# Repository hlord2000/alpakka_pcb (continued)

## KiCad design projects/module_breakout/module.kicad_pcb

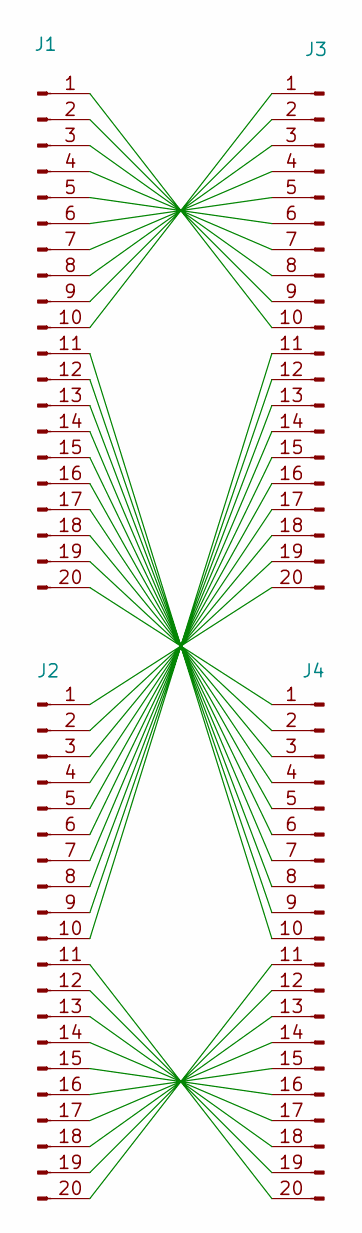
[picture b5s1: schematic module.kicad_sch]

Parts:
J1, J2: Conn_01x20_Pin; Hirose_DF12NB_receptacle; LCSC C2917814
J3, J4: Conn_01x20_Pin; PinHeader_1x20_P2.54mm_Vertical

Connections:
unnamed: J1.1, J3.10
unnamed: J1.2, J3.9
unnamed: J1.3, J3.8
unnamed: J1.4, J3.7
unnamed: J1.5, J3.6
unnamed: J1.6, J3.5
unnamed: J1.7, J3.4
unnamed: J1.8, J3.3
unnamed: J1.9, J3.2
unnamed: J1.10, J3.1
unnamed: J1.11, J4.10
unnamed: J1.12, J4.9
unnamed: J1.13, J4.8
unnamed: J1.14, J4.7
unnamed: J1.15, J4.6
unnamed: J1.16, J4.5
unnamed: J1.17, J4.4
unnamed: J1.18, J4.3
unnamed: J1.19, J4.2
unnamed: J1.20, J4.1
unnamed: J2.1, J3.20
unnamed: J2.2, J3.19
unnamed: J2.3, J3.18
unnamed: J2.4, J3.17
unnamed: J2.5, J3.16
unnamed: J2.6, J3.15
unnamed: J2.7, J3.14
unnamed: J2.8, J3.13
unnamed: J2.9, J3.12
unnamed: J2.10, J3.11
unnamed: J2.11, J4.20
unnamed: J2.12, J4.19
unnamed: J2.13, J4.18
unnamed: J2.14, J4.17
unnamed: J2.15, J4.16
unnamed: J2.16, J4.15
unnamed: J2.17, J4.14
unnamed: J2.18, J4.13
unnamed: J2.19, J4.12
unnamed: J2.20, J4.11

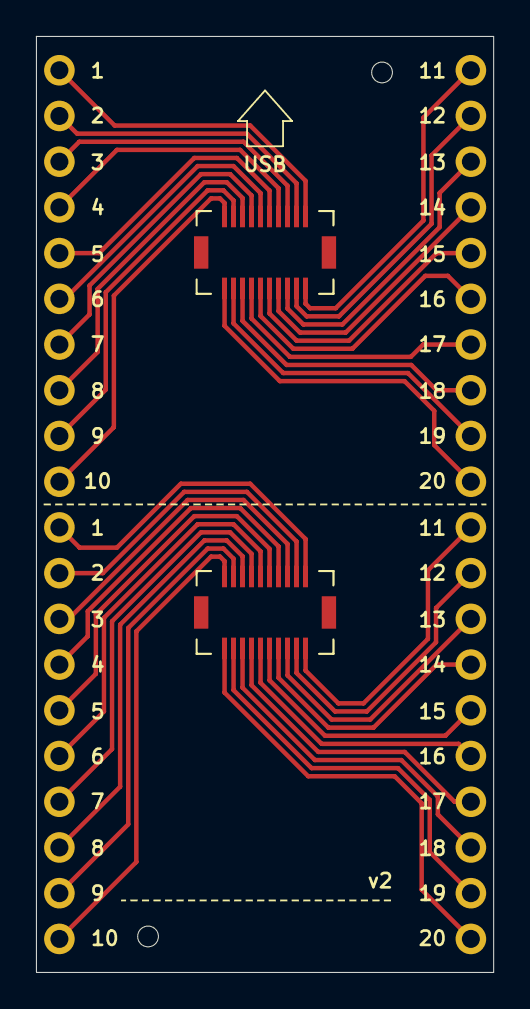
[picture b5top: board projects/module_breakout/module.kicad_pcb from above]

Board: 2 copper layers, 25.4 x 52.0 mm, 4 parts (0 on the bottom side), 40 nets.

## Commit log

2024-04-19 RF module test 1
2024-06-14 Added breakout module. Added custom thin header holes. Sunk USB-C
2024-07-02 RF module test 4
2024-07-15 RF module test 5
2024-07-22 RF module test 6
2024-08-05 RF module test 7
2024-09-03 Alpakka board RF proto
2024-09-11 RF module test 7.5
2024-09-18 RF test A2
2024-09-19 RF module test 8
2024-09-19 RF test A2 final
2024-10-22 RF module test 9
2024-11-06 RF module test 10
2024-12-10 Remove breakout boards from projects
2024-12-10 Renamed module to marmota
2024-12-10 Changed debug port to header pins, Changed nets from global to local
2024-12-11 1M touch resistor with optional 500K mode
2024-12-12 Battery connector silk placement and 3D model
2024-12-17 Voltage divider and read on the ESP, Thermal relief for the ESP
2024-12-17 New arrangement for buckboost, Added 2nd vcc capacitor
2024-12-19 Added I2C pullups
2024-12-20 MCP without inner traces, Richtek rearrange
2024-12-23 Bigger footprint inductor
2024-12-23 Extra GPIO exposed to connector, Ground plane tweaks
2024-12-23 Thumbsticks without far caps, Thumbstick test points, Scrollwheel support dedicated holes
2024-12-26 Added battery test point, Layout tweaks
2024-12-26 Updated hardware generation detection
2024-12-30 Adjusted scrollwheel support holes position
2025-01-02 Changed power output caps to 47uF in 0603 footprint
2025-01-02 Remove DNP resistor from BOM
2025-01-07 Readjusted scroll holder holes
2025-01-07 Fixed export script rotation in bottom layer, Fixed L1R1 switch origin
2025-01-14 Using Richtek 6150 instead of 6160
2025-01-14 Richtek power saving high, Tweaks
2025-01-19 Shifted GPIO nets on the bottom row of the top connector
2025-02-03 Marmota RT6150 power save mode enabled, Replacement for crystal oscillator
2025-02-04 Alpakka added touch ref path, Reordered debug pins, Swapped analog 2-3, Removed wheel support holes, Added silkscreen
2025-02-09 Fix Alpakka thumbstick TP silkscreen
2025-02-09 Marmota added 3V3 test point
2025-02-25 Connected RT buckboost power save pin to gpio, Shifted GPIOs
2025-02-25 Usb connector smaller holes
2025-02-26 Marmota ESP EN weak pull down
2025-02-26 Alpakka revert to single touch path, Shifted GPIOs to match Marmota
2025-02-26 Marmota tweaked ESP EN arrangement
2025-02-26 RP2040 locked internal routing
2025-02-27 Better Marmota v-cut indications
2025-02-27 Do not export drill marks
2025-03-13 Alpakka edge rails, USB indication silkscreen
2025-03-13 Fixed Marmota schematic parity
2025-03-14 Alpakka additional v-cut silkscreen
2025-03-31 Added manual mouse bites to Alpakka rails
2025-07-02 Initial schematic for nRF52840+nPM1300
2025-07-03 Reworked Alpakka w/ interrupt lines, etc
2025-07-05 Updated for nRF52840
